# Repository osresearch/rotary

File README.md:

This is an extension on Adafruit's [`FONAtest.ino`](https://github.com/adafruit/Adafruit_FONA/blob/master/examples/FONAtest/FONAtest.ino)
example code to allow it to be used with a rotary phone.  The Teensy
2.0 decodes the pulses and implements the state machine to allow you to
place outbound phone calls.  In-bound calls are working and can activate
the ringer when on USB power, but the boost converter circuit is a work
in progress.

The dialtone is generated by the FONA and under control of the teensy,
but ringing and dialing is done by the cell network.  There is not a
proper "off hook" tone in the FONA, so the closest version was used.

Since the entire phone number must be passed to the `ATDT` command
string, the system must try to detect when the user is done dialing.
There is currently a multi-second delay after the last number.

During a call pulses will be translated to DTMF, but the user will
not hear them on the handset.  There is also no comfort tone, which
makes using the phone feel "dead".

Wiring
===

* Teensy Gnd -> FONA Ground, FONA Key, Phone F (blue?)
* Teensy Vcc -> FONA Vio
* Teensy Pin 0 -> FONA Reset
* Teensy Pin 1 -> Phone RR (green on the dial), rotary dial
* Teensy Pin 2 -> Phone L1 (RJ45 green), hook relay
* Teensy Pin 6 -> FONA Ring indicator
* Teensy Pin 7 -> FONA RX
* Teensy Pin 8 -> FONA TX
* Teensy Pin 9 -> boost converter pwm
* Teensy Pin A0 -> boost converter voltge divider

The boost converter circuit needs to be drawn.

Note the [FONA 32u4 pinout](https://learn.adafruit.com/adafruit-feather-32u4-fona/pinouts) is a bit different:

* GPIO 8 -> FONA TXD (Soft Serial)
* GPIO 9 -> FONA RXD (Soft Serial)
* GPIO 7 -> FONA Ring Indicator
* GPIO 4 -> FONA Reset

Todo
===

* Redial support.
* ~~Incoming call state machine~~ - Done. Incoming calls works (although they play a tone in the speaker)
* ~~Disable headset ring tone.~~ - WONTFIX, since the bell overpowers it quite easily.
* Ringer driver circuit. Looks like 15V will engage the bell solenoid, so a simple charge pump and low frequency PWM should do it. -- Almost done, need to find parameters to work with 3.7V LiPo.
* ~~PCB design to mount FONA, Teensy and wire headers for the phone connections. -- Started in `pcb/rotaryfona.sch`, but no where near ready.~~ On hold since the FONA 32u4 has a MCU built in.
* Package everything to fit into the phone.
* Buy a red phone, cut a hole for USB charging cable.
* Teensy powered from the battery?  Battery switch?
* Figure out why 300 baud isn't working with the FONA as well as it did with my cellphone.
* Text to speech for SMS received - only supported in the 800H, not the 800L.

State Machine
==

The rotary phone code is implemented as a state machine to try to
keep it clean and easy to extend. Unfortunately there isn't an easy way
to round trip from the code to this diagram, so it doesn't exactly match
the executable code in [`Rotary.cpp`](./RotaryFona/Rotary.cpp).
Also, nearly every state other than `RINGING` has an implicit edge
back to `ON_HOOK` if the user hangs up the phone while in that state.

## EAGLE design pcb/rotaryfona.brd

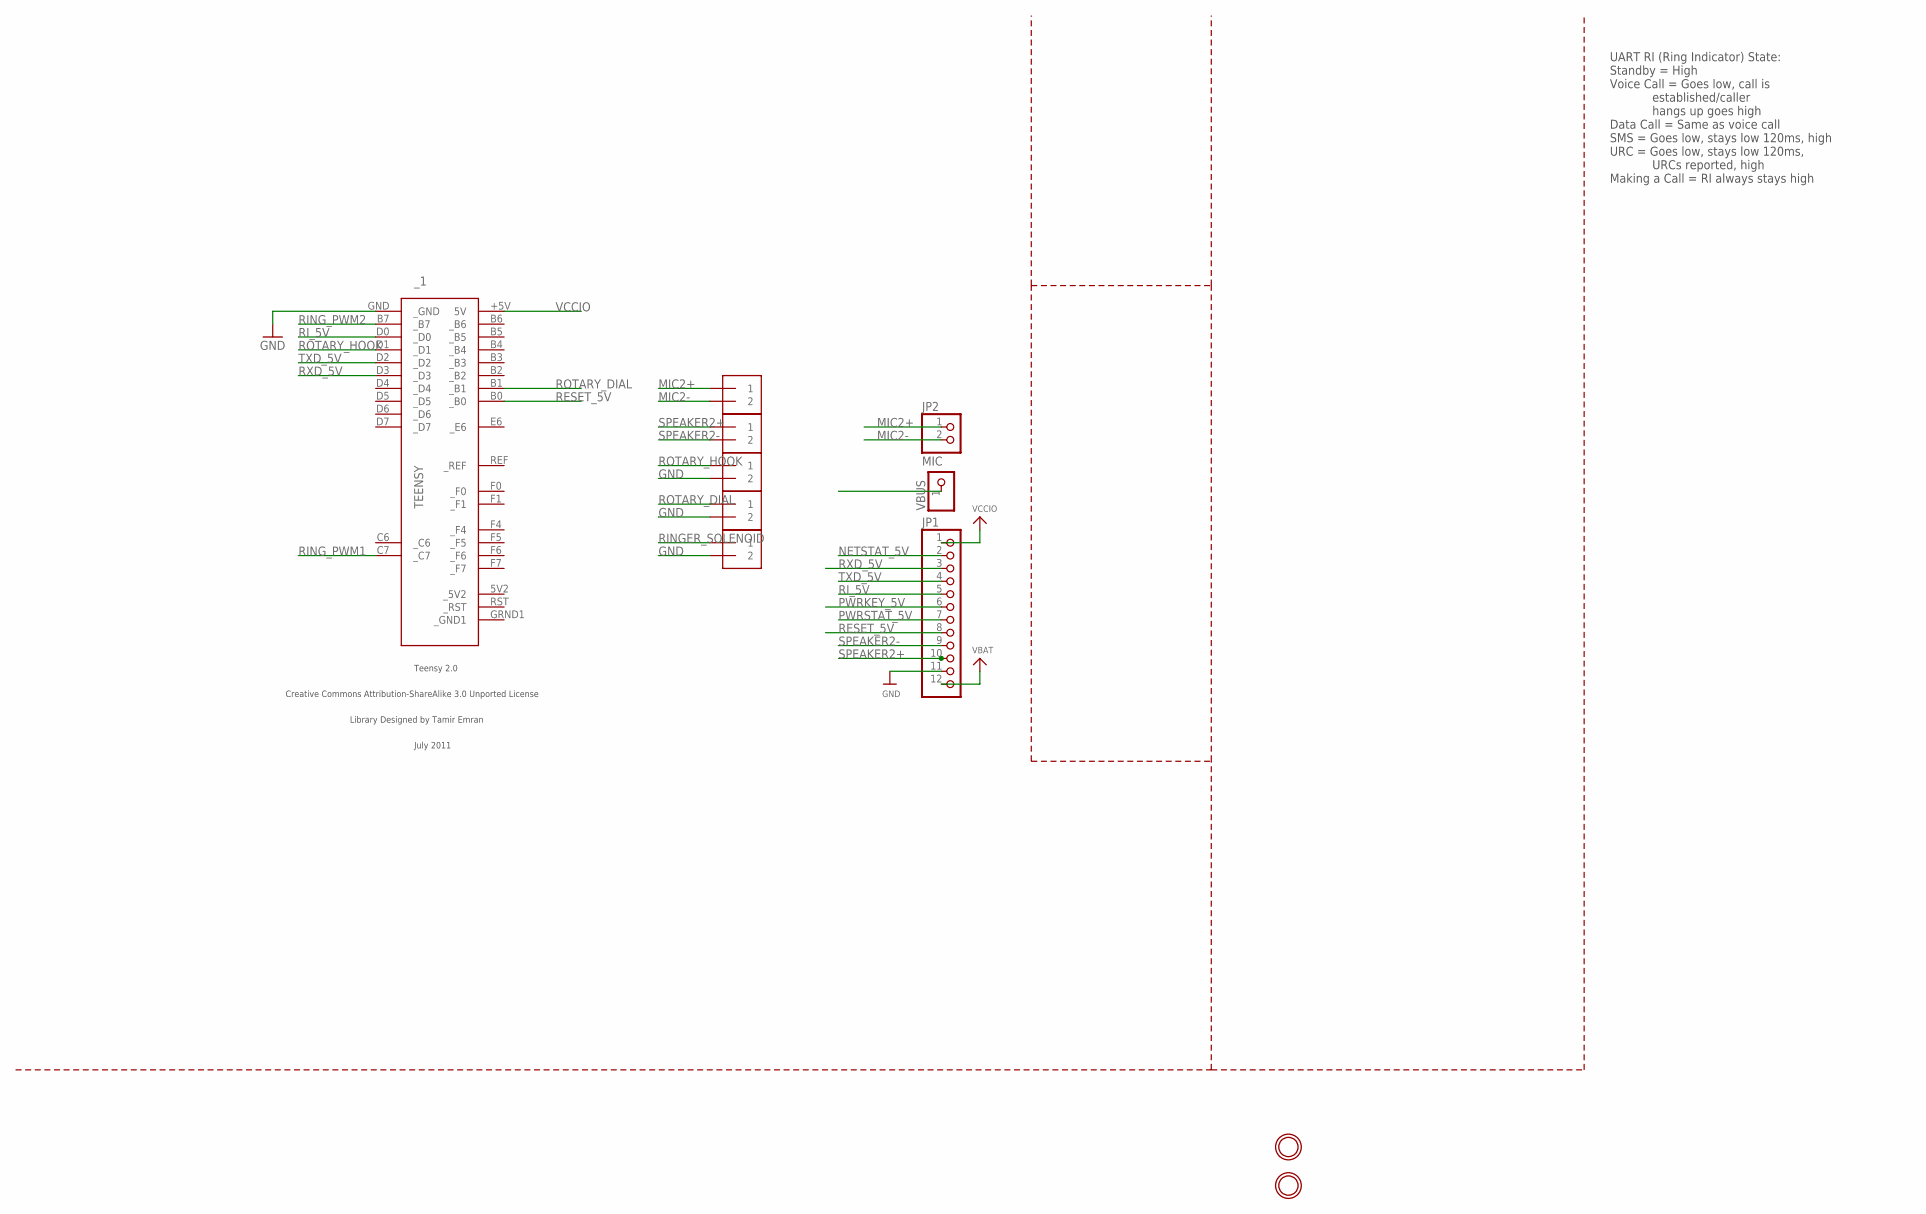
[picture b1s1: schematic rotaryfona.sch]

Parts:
DIAL: 1X2-3.5MM
HOOK: 1X2-3.5MM
JP1: PINHD-1X12-CB; 1X12-CB
JP2: MIC; 1X02_ROUND
MIC: 1X2-3.5MM
RINGER: 1X2-3.5MM
SPK: 1X2-3.5MM
U$33, U$34: MOUNTINGHOLE2.5; MOUNTINGHOLE_2.5_PLATED
VBUS: PINHD-1X1CB; 1X01-CLEANBIG
_1: TEENSY

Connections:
GND: DIAL.2, HOOK.2, JP1.11, RINGER.2, _1.GND (_GND)
MIC2+: JP2.1, MIC.1
MIC2-: JP2.2, MIC.2
NETSTAT_5V: JP1.2
PWRKEY_5V: JP1.6
PWRSTAT_5V: JP1.7
RESET_5V: JP1.8, _1.B0 (_B0)
RINGER_SOLENOID: RINGER.1
RING_PWM1: _1.C7 (_C7)
RING_PWM2: _1.B7 (_B7)
RI_5V: JP1.5, _1.D0 (_D0)
ROTARY_DIAL: DIAL.1, _1.B1 (_B1)
ROTARY_HOOK: HOOK.1, _1.D1 (_D1)
RXD_5V: JP1.3, _1.D3 (_D3)
SPEAKER2+: JP1.10, SPK.1
SPEAKER2-: JP1.9, SPK.2
TXD_5V: JP1.4, _1.D2 (_D2)
VBAT: JP1.12
VCCIO: JP1.1, _1.+5V (5V)

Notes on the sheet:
UART RI (Ring Indicator) State: Standby = High Voice Call = Goes low, call is established/caller hangs up goes high Data Call = Same as voice call SMS = Goes low, stays low 120ms, high URC = Goes low, stays low 120ms, URCs reported, high Making a Call = RI always stays high

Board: 2 copper layers, 11 parts (0 on the bottom side), 12 nets, no tracks yet.

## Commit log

2017-03-03 started on pulse decoding
2017-03-03 longer delays, decoding works
2017-03-04 import of Adafruit fona test example
2017-03-04 update Fona example to include rotary dial decoding
2017-03-04 Implemented rotary phone logic as a state machine.
    All states work, except for the initial dial which
    seems to have issues if the dialtone is still playing
    due to the adafruit library taking CPU time away.
2017-03-04 add hangup detection, better tone stopping
2017-03-04 remove prototype code
2017-03-05 document wiring
2017-03-05 more images
2017-03-05 one more todo
2017-03-05 license import
2017-03-05 link to fonatest
2017-03-05 more details
2017-03-05 incoming calls work
2017-03-05 started on PCB, importing from adafruit fona board design
2017-03-05 ignore temp files
2017-03-05 split rotary code into a separate class
2017-03-05 Timer3 based boost converter to drive the phone ringer (not yet functional)
2017-03-05 Ringer circuit works.
    This uses the PWM on timer3 to pin9, which allows us to have a 100 KHz
    PWM output to the ringer. We've also used the FONA ring indicator
    pin instead of polling the status, which gives us a faster response
    and might allow us to sleep while waiting for calls.
2017-03-06 state machine diagram
2017-03-06 start initialization before the USB is set
2017-03-06 state diagram
2017-03-06 Fix link to state diagram
2017-03-06 Implicit link to ON_HOOK
2017-03-06 tweak timings for boost converter, still does not work on battery
2017-03-07 dual MOSFET tests generate 35V from 5V with 47uH coil at 2usec/934ticks
2017-03-07 improve low voltage charge pump by allow more charge time
2017-03-10 move charge pump code into the ringer logic. seems to work!
2017-03-11 FONA 32u4 pinout
2017-03-11 TTS note
2017-03-18 separate tuning module, update wiring for feather fona

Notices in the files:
parts and their libraries:
microbuilder: This work is placed in the public domain, and may be freely used for commercial and non-commercial work with the following conditions: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
teensy: Creative Commons Attribution-ShareAlike 3.0 Unported License
